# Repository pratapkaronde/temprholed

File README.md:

# temprholed
Atmega Board for Temperature and Relative Humidity monitor on OLED

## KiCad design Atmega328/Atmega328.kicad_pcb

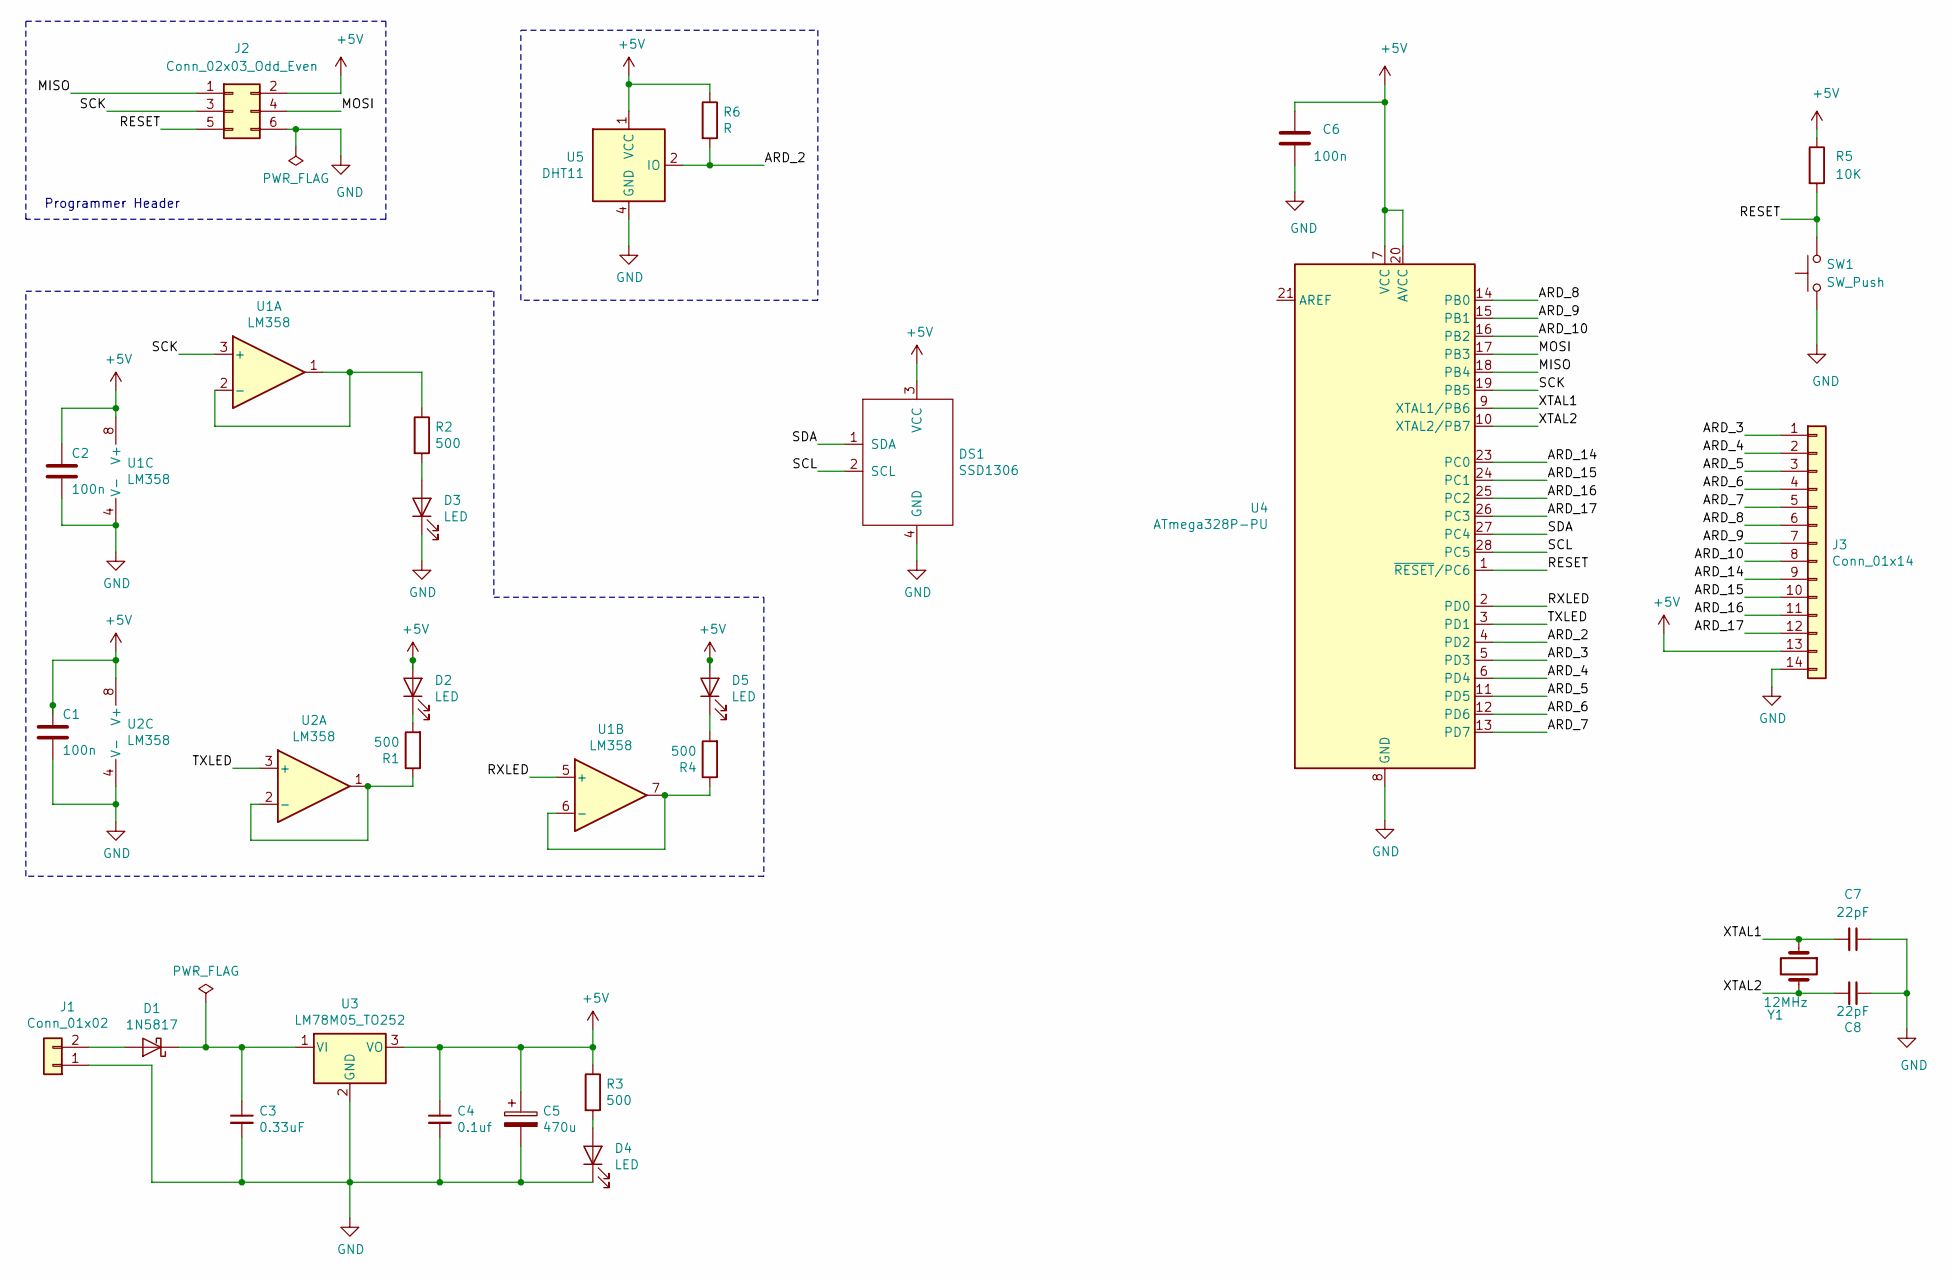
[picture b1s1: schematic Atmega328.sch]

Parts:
C1, C2, C6: 100n; C_0805_2012Metric
C3: 0.33uF; C_0805_2012Metric
C4: 0.1uf; C_0805_2012Metric
C5: 470u; CP_Radial_D4.0mm_P2.00mm
C7, C8: 22pF; C_0805_2012Metric
D1: 1N5817; D_DO-34_SOD68_P7.62mm_Horizontal
D2, D3, D4, D5: LED; LED_0805_2012Metric
DS1: SSD1306; SSD1396
J1: Conn_01x02; JST_EH_B2B-EH-A_1x02_P2.50mm_Vertical
J2: Conn_02x03_Odd_Even; IDC-Header_2x03_P2.54mm_Vertical
J3: Conn_01x14; PinSocket_1x14_P2.54mm_Vertical
R1, R2, R3, R4: 500; R_0805_2012Metric
R5: 10K; R_0805_2012Metric
R6: R; R_0805_2012Metric
SW1: SW_Push; SW_PUSH_6mm
U1, U2: LM358; SOIC-8_3.9x4.9mm_P1.27mm
U3: LM78M05_TO252; TO-252-2
U4: ATmega328P-PU; DIP-28_W7.62mm
U5: DHT11; Aosong_DHT11_5.5x12.0_P2.54mm
Y1: 12MHz; Crystal_HC49-4H_Vertical

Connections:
+5V: C1.1, C2.1, C4.1, C5.1, C6.1, D2.2 (A), D5.2 (A), DS1.3 (VCC), J2.2, J3.13, R3.1, R5.1, R6.1, U1.8 (V+), U2.8 (V+), U3.3 (VO), U4.7 (VCC), U4.20 (AVCC), U5.1 (VCC)
/ARD_2: R6.2, U4.4 (PD2), U5.2 (IO)
/ARD_3: J3.1, U4.5 (PD3)
/ARD_4: J3.2, U4.6 (PD4)
/ARD_5: J3.3, U4.11 (PD5)
/ARD_6: J3.4, U4.12 (PD6)
/ARD_7: J3.5, U4.13 (PD7)
/ARD_8: J3.6, U4.14 (PB0)
/ARD_9: J3.7, U4.15 (PB1)
/ARD_10: J3.8, U4.16 (PB2)
/ARD_14: J3.9, U4.23 (PC0)
/ARD_15: J3.10, U4.24 (PC1)
/ARD_16: J3.11, U4.25 (PC2)
/ARD_17: J3.12, U4.26 (PC3)
/MISO: J2.1, U4.18 (PB4)
/MOSI: J2.4, U4.17 (PB3)
/RESET: J2.5, R5.2, SW1.2, U4.1 (~RESET~/PC6)
/RXLED: U1.5 (+), U4.2 (PD0)
/SCK: J2.3, U1.3 (+), U4.19 (PB5)
/SCL: DS1.2 (SCL), U4.28 (PC5)
/SDA: DS1.1 (SDA), U4.27 (PC4)
/TXLED: U2.3 (+), U4.3 (PD1)
/XTAL1: C7.2, U4.9 (XTAL1/PB6), Y1.1
/XTAL2: C8.2, U4.10 (XTAL2/PB7), Y1.2
GND: C1.2, C2.2, C3.2, C4.2, C5.2, C6.2, C7.1, C8.1, D3.1 (K), D4.1 (K), DS1.4 (GND), J1.1, J2.6, J3.14, SW1.1, U1.4 (V-), U2.4 (V-), U3.2 (GND), U4.8 (GND), U4.22 (GND), U5.4 (GND); also elsewhere on the board
unnamed: C3.1, D1.1 (K), U3.1 (VI)
unnamed: D1.2 (A), J1.2
unnamed: D2.1 (K), R1.2
unnamed: D3.2 (A), R2.2
unnamed: D4.2 (A), R3.2
unnamed: D5.1 (K), R4.2
unnamed: R1.1, U2.1, U2.2 (-)
unnamed: R2.1, U1.1, U1.2 (-)
unnamed: R4.1, U1.6 (-), U1.7

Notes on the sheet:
Programmer Header

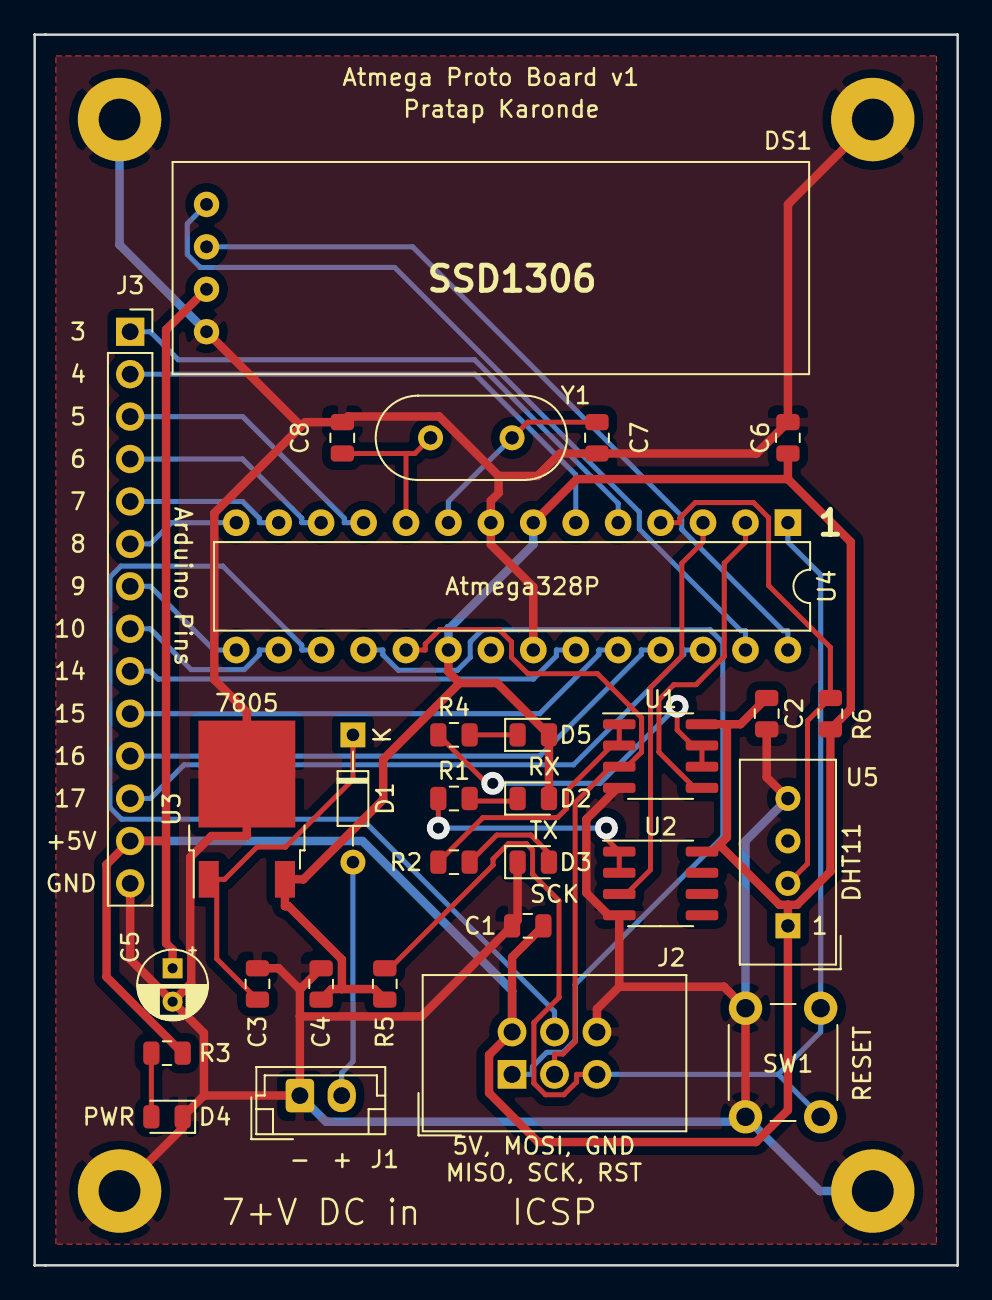
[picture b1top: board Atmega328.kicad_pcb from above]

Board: 2 copper layers, 55.2 x 73.7 mm, 34 parts (0 on the bottom side), 34 nets.

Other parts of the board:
M1, M2, M3, M4: MountingHole_2.5mm_Pad

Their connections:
GND: M1.1, M2.1, M3.1, M4.1; also elsewhere on the board

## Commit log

2019-08-13 Add .gitignore
2019-08-14 Cleanup and Test checkin
2019-08-14 Some more cleanup
2019-08-17 Adding KiCAD Board Files
2019-08-17 Add KiCAD files
2019-08-17 Add Ground Zone on the back
2019-08-26 Fix footprints
2019-08-29 PCB Cleanup and Ready
2019-09-20 Debug using OLED
2019-09-23 Change the array handling. Add Debug Code
